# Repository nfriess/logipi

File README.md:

# Code for Logipi FPGA board

This project contains various bits of code for the logpi board.
More information on the board can be found at
http://valentfx.com/logi-pi/

## Projects

- **audio_player**: A basic implementation to stream hifi
  audio from a host PC to a logipi that drives 8 D-to-As.

- **flash_loader**: A utility to load .bit files on the flash
  chip, or read data from the flash chip.

- **i2cslave**: An I2C slave device that can communicate with
  the Raspberry Pi, implementing a wishbone master in VHDL.

- **pi_audio_player**: Playing hifi audio from the Raspberry Pi,
  replacing the audio_player setup with C# and Ethernet.

- **spislave**: An SPI slave device that can communicate with
  the Raspberry Pi, implementing a wishbone master in VHDL.

## License

**Licensed under the GNU GENERAL PUBLIC LICENSE version 2**

Copyright (C) 2016-2017  Nathan Friess

This program is free software; you can redistribute it and/or
modify it under the terms of the GNU General Public License
as published by the Free Software Foundation; either version 2
of the License, or (at your option) any later version.

This program is distributed in the hope that it will be useful,
but WITHOUT ANY WARRANTY; without even the implied warranty of
MERCHANTABILITY or FITNESS FOR A PARTICULAR PURPOSE.  See the
GNU General Public License for more details.

You should have received a copy of the GNU General Public License
along with this program; if not, write to the Free Software
Foundation, Inc., 51 Franklin Street, Fifth Floor, Boston, MA  02110-1301, USA.

http://www.gnu.org/licenses/old-licenses/gpl-2.0-standalone.html

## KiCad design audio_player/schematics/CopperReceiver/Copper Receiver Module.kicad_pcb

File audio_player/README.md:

# Hi-fi Audio Player

A friend of mine has been building Hi-fi audio systems for
a very long time.  Before this project started, his current
system used a custom-designed board around a USB device to
stream audio from a host Windows PC to his custom-built
amplifiers.  Over time the USB device has become too
cumbersome so I have helped design a replacement setup
that will drive his amplifiers using a Logi-PI board.

This project is quite complex so more detailed documentation
is available in the doc directory.

## Architecture

### Hi-fi System

I am not an audiophile, nor do I know the intricacies of
audio amplifier design.  My friend has built some of the
highest quality amplifiers around.

For my part of this system, the only aspects that I need
to know are that there are 8 amplifiers (channels), each
driving a speaker.  The input of an amplifier is an AD1862
D-to-A, which accepts a 20-bit audio.  The Latch Enable
pin is driven by a 44.1 KHz clock, which is divided down
in the FPGA from a standard 16.9344 MHz crystal oscillator.

### Host PC

My friend has written his own audio player program in
C# that he currently uses to stream audio to the Hi-fi
system.  The program reads in raw .WAV files containing
2 channel, 16-bit, 44.1 KHz audio.  It then converts this
to the 8-channel, 20-bit format that will be consumed by
the D-to-As.  It then sends this data over USB, to an
FPGA that drives the D-to-As.

The source code for my friend's audio player is not
available in this repository because that belongs to him.
The project here has a very simple C# program that will
drive the FPGA on the Logi-PI over an Ethernet connection.
He has then taken the core C# class that handles all of the
logic for the Ethernet protocol and integrated that into
his audio player program.

## Logi-Pi Board

Everything in between the host PC and D-to-As, and the
central part of this project.

Although the Logi-Pi board is often paired with a Raspberry
Pi, the Raspberry Pi is is actually not used in the final
product. Instead, a Pi is used to program the flash chip on
the Logi-PI board and was used to debug the VHDL by
monitoring various registers defined in the VHDL.

Other key components required for this project are:

* Digilent PmodNIC100, an add-on board designed around the
  Microchip ENC424J600 Ethernet controller.

* An external 16.9344 MHz crystal to drive the FPGA (for
  proper hi-fi audio).  The FPGA can generate an internal
  clock that is very close to 16.9334 MHz for testing
  purposes.

## Digital Crossover Demo

All of the main parts of this project are focused on the
hardware side, using the Logi-Pi board to drive multiple
DACs.  The "sw" directory provides a minimal example of a
C# program that will transmit audio data to the Logi-Pi
board.  In the final setup of the Hi-fi system, my friend
is driving 6 (and later 8) amplifiers, each outputting only
the ideal frequency range for a particular driver (speaker).
So insteead of using physical parts to create a crossover
for each driver, we do this in C# and send the individual
channel data to the Logi-Pi board, which then drives 6 DACs
independently.

The DigitalCrossoverDemo directory provides an example of
a digital crossover created in C#.  This program does not
work with the Logi-Pi board directly.  Instead it can be
used to listen to and and visual the results of using the
digital crossover code.  It should be trivial to plug this
demo code into the simple player in the sw directory.

The digital crossover is implemented as a chain of audio
filters, following a similar producer-consumer format to
C# Stream sub-classes.  Also included in this project are
a number of other helpful audio filters, such as a volume
control and de-emphasis filter.

The code for crossover filters and de-emphasis filter was
written by Leonard Manzara in C, and ported to C# by me.

## DAC Receiver Board

In the schematics directory is the design for the DAC
receiver board.  That board is part of each amplifier and
is responsible to receive the signals from the Logi-Pi
board and use them to drive the D-to-A in the amplifier.
It uses opto-isolators to keep any electrical noise from
the Logi-Pi separate from the D-to-A.  It also has the
voltage regulators necessary to provide power to the
digital side of the D-to-A.

The voltage regulators are chosen as LT3042 as those are
considered to be some of the best regulators based on
discussions at diyaudio.com.

NOTE: The 47uF capacitors shown in the design are 6V
tolerant but need to be 12V tolerant.  In the next revision
we will need to use a larger footprint on the board to
accommodate the correct capacitor.

## License

### External Libraries

Several pieces of code in VHDL and Verilog were borrowed
from external sources.  Those files will have their own
copyright notices and licenses in the file headers.

These include:

* sdram_controller.v - From opencores.org, GPL license.
  Has been modified slightly to interoperate with other
  parts of the VHDL project.

* control_pack.vhd, logi_primitive_pack.vhd, logi_utils_pack.vhd
  logi_wishbone_pack.vhd, logi_wishbone_peripherals_pack.vhd,
  logipi_r1_5.ucf, spi_wishbone_wrapper.vhd, wishbone_register.vhd:
  From the Logi-PI example code.  Modifed in several places.

* syncflag.vhd, syncsignal.vhd - Based on designs at
  http://www.fpga4fun.com/CrossClockDomain1.html

* dp_sram.vhd - From opencores.org, GPL license.

### New code

Other than the above code, any code produced by me is licensed
as:

**Licensed under the GNU GENERAL PUBLIC LICENSE version 2**

Copyright (C) 2016-2017  Nathan Friess

This program is free software; you can redistribute it and/or
modify it under the terms of the GNU General Public License
as published by the Free Software Foundation; either version 2
of the License, or (at your option) any later version.

This program is distributed in the hope that it will be useful,
but WITHOUT ANY WARRANTY; without even the implied warranty of
MERCHANTABILITY or FITNESS FOR A PARTICULAR PURPOSE.  See the
GNU General Public License for more details.

You should have received a copy of the GNU General Public License
along with this program; if not, write to the Free Software
Foundation, Inc., 51 Franklin Street, Fifth Floor, Boston, MA  02110-1301, USA.

http://www.gnu.org/licenses/old-licenses/gpl-2.0-standalone.html

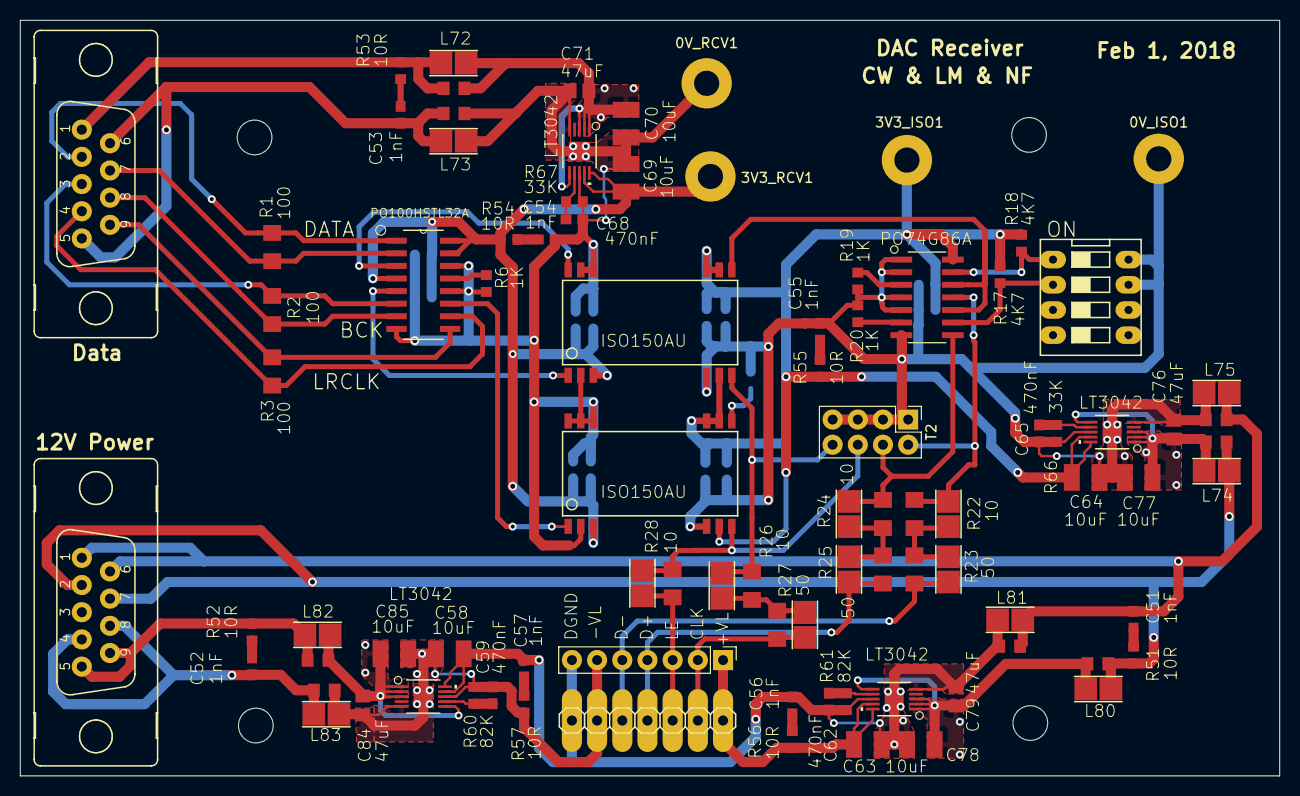
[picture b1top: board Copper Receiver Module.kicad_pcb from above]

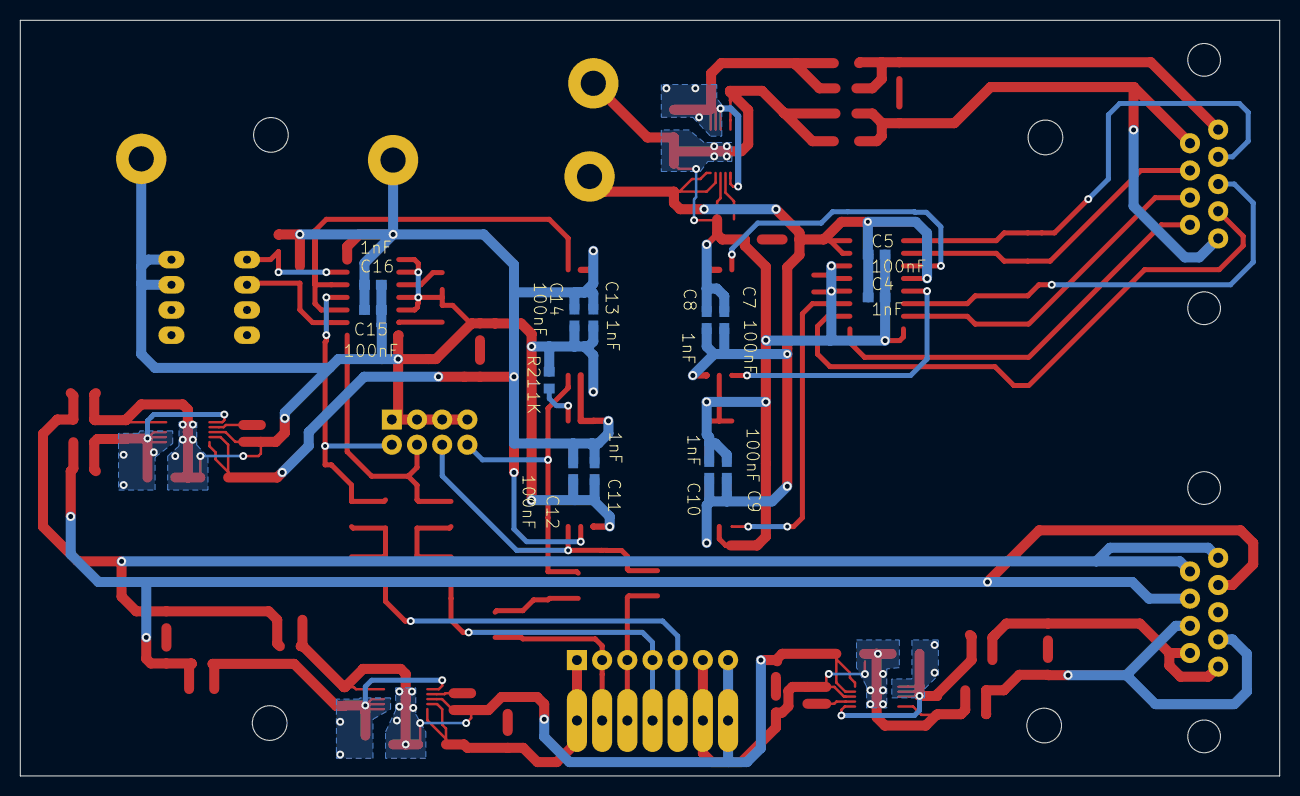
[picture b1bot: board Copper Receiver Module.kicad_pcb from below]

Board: 2 copper layers, 127.0 x 76.2 mm, 103 parts (13 on the bottom side), 55 nets.

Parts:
0V_ISO1, 0V_RCV1, 3V3_ISO1, 3V3_RCV1: Conn_01x01_Female; SinglePad
C4, C8, C10, C11, C13, C16, C51, C52, C53, C54, C55, C56, C57: 1nF; C0603
C5, C7, C9, C12, C14, C15: 100nF; C0603
C58, C63, C64, C69, C70, C77, C78, C85: 10uF; C1210
C59, C62, C65, C68: 470nF; C0603
C71, C76, C79, C84: 47uF; C0805
IC1, IC2, IC3, IC4: LT3042; MSOP-10_MSE
IC5: PO100HSTL32A; SOIC-16
IC7: PO74G86A; SO-14
ISO1, ISO2: ISO150AU; SO28-3-ISO150
JP1: LRCLK; SOLDER-JUMPER_1-WAY
JP2: D-; SOLDER-JUMPER_1-WAY
JP3: D+; SOLDER-JUMPER_1-WAY
JP4: CLK; SOLDER-JUMPER_1-WAY
JP13, JP14, JP15, JP72, JP73, JP74, JP75, JP80, JP81, JP82, JP83: JUMPER-SMT_2_NO_SILK; SOLDER-JUMPER_1-WAY
L72, L73, L74, L75, L80, L81, L82, L83: 60/20/5; RESC0805_N
R1, R2, R3: 100; R1206
R6, R19, R20, R21: 1K; R0603
R17, R18: 4K7; R0603
R22, R24, R26, R28: 10; R1206
R23, R25, R27: 50; R1206
R51, R52, R53, R54, R55, R56, R57: 10R; R0603
R60, R61: 82K; R0603
R66, R67: 33K; R0603
S1: DS04; DS-04_Larger
T1: TERM_07HOLES; TERM_07_HOLES_LARGER
T2: Conn_02x04_Counter_Clockwise; Header_2x4_Larger
T3: Conn_01x07; Pin_Header_1x7_Larger
X1, X2: SubD9; SubD9_Larger

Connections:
0V_ISO: 0V_ISO1.1, C11.2, C12.2, C13.2, C14.2, C15.2, C16.2, C55.2, C64.2, C65.2, C76.2, C77.2, IC4.5, IC4.8, IC4.11, IC7.1, IC7.2, IC7.4, IC7.5, IC7.7, ISO1.12, ISO2.12, JP75.2, L75.1, R19.1, R20.1, R21.1, R66.1, S1.7, S1.8, T2.1, T2.3, T2.5, T2.7
0V_RAW_RECV: C53.2, JP73.1, L73.2, X2.5, X2.6
0V_RECV: 0V_RCV1.1, C4.2, C5.2, C7.2, C8.2, C9.2, C10.2, C54.2, C68.2, C69.2, C70.2, C71.2, IC1.5, IC1.8, IC1.11, IC5.8, IC5.12, IC5.14, ISO1.2, ISO1.26, ISO1.27, ISO2.2, ISO2.26, ISO2.27, ISO2.28, JP73.2, L73.1, R6.1, R67.1
5V_RAW_RECV: JP72.1, L72.2, R53.2, X2.1
+3.3V_ISO: 3V3_ISO1.1, C11.1, C12.1, C13.1, C14.1, C15.1, C16.1, C64.1, IC4.9, IC4.10, IC7.14, ISO1.13, ISO1.16, ISO1.17, ISO2.13, ISO2.16, ISO2.17, R17.1, R18.1, R55.2
+3.3V_RECV: 3V3_RCV1.1, C4.1, C5.1, C7.1, C8.1, C9.1, C10.1, C69.1, IC1.9, IC1.10, IC5.4, IC5.15, IC5.16, ISO1.3, ISO2.3, R54.2
+8.2V_DAC: C63.1, IC2.9, IC2.10, R56.2, T1.+VL, T3.1
-8.2V_DAC: C58.2, C59.2, C84.2, C85.2, IC3.5, IC3.8, IC3.11, JP83.2, L83.1, R57.1, R60.1, T1.-VL, T3.6
/Decoding/BCK+: IC5.6, R2.1, X2.3
/Decoding/D+: JP15.1, R25.1, T1.D+, T3.4
/Decoding/D-: JP14.1, R23.1, T1.D-, T3.5
/Decoding/DATA: IC7.10, IC7.12, ISO1.15
/Decoding/DATA+: IC5.2, R1.2, X2.7
/Decoding/LRCK+: IC5.10, R3.2, X2.4
/Regulated DC Power/1_RAW_0V: C51.2, JP75.1, JP81.1, L75.2, L81.2, X1.1, X1.6
/Regulated DC Power/1_RAW_+12V: JP74.1, JP80.1, L74.2, L80.2, R51.2, X1.2, X1.7
/Regulated DC Power/2_RAW_0V: C52.2, JP83.1, L83.2, X1.4, X1.8
/Regulated DC Power/2_RAW_+12V: JP82.1, L82.2, R52.2, X1.5, X1.9
DGND_DAC: C56.2, C57.2, C58.1, C62.2, C63.2, C78.2, C79.2, IC2.5, IC2.8, IC2.11, IC3.9, IC3.10, JP81.2, L81.1, R61.1, T1.DGND, T3.7
unnamed: C51.1, R51.1
unnamed: C52.1, R52.1
unnamed: C53.1, R53.1
unnamed: C54.1, R54.1
unnamed: C55.1, R55.1
unnamed: C56.1, R56.1
unnamed: C57.1, R57.2
unnamed: C59.1, IC3.7, R60.2
unnamed: C62.1, IC2.7, R61.2
unnamed: C65.1, IC4.7, R66.2
unnamed: C68.1, IC1.7, R67.2
unnamed: C70.1, C71.1, IC1.1, IC1.2, IC1.3, IC1.6, JP72.2, L72.1
unnamed: C76.1, C77.1, IC4.1, IC4.2, IC4.3, IC4.6, JP74.2, L74.1
unnamed: C78.1, C79.1, IC2.1, IC2.2, IC2.3, IC2.6, JP80.2, L80.1
unnamed: C84.1, C85.1, IC3.1, IC3.2, IC3.3, IC3.6, JP82.2, L82.1
unnamed: IC5.1, R1.1, X2.2
unnamed: IC5.3, ISO1.28
unnamed: IC5.5, ISO1.1
unnamed: IC5.7, R2.2, X2.8
unnamed: IC5.9, R3.1, X2.9
unnamed: IC5.11, ISO2.1
unnamed: IC5.13, R6.2
unnamed: IC7.3, R19.2
unnamed: IC7.6, R20.2
unnamed: IC7.8, JP3.2, R24.2, T2.4
unnamed: IC7.9, R17.2, S1.2
unnamed: IC7.11, JP2.2, R22.2, T2.2
unnamed: IC7.13, R18.2, S1.1
unnamed: ISO1.14, JP4.2, R26.1, T2.8
unnamed: ISO2.14, JP1.1, R28.1, T2.6
unnamed: ISO2.15, R21.2
unnamed: JP1.2, R28.2, T1.LE, T3.3
unnamed: JP13.1, R27.2, T1.CLK, T3.2
unnamed: JP4.1, JP13.2, R26.2, R27.1
unnamed: JP2.1, JP14.2, R22.1, R23.2
unnamed: JP3.1, JP15.2, R24.1, R25.2

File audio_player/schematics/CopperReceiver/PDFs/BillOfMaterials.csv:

"Source:","D:\Users\Natman\Documents\KiCad\CopperReceiver\Copper Receiver Module.sch"
"Date:","2/15/2018 6:56:26 PM"
"Tool:","Eeschema (2018-01-07 revision 6cee19d37)-makepkg"
"Component Count:","103"
"Ref","Value","Footprint","Datasheet","Manufacturer","Vendor"
"0V_ISO1","Conn_01x01_Female","CustomParts:SinglePad","","",""
"0V_RCV1","Conn_01x01_Female","CustomParts:SinglePad","","",""
"3V3_ISO1","Conn_01x01_Female","CustomParts:SinglePad","","",""
"3V3_RCV1","Conn_01x01_Female","CustomParts:SinglePad","","",""
"C4","1nF","Capacitors_SMD:C_0603","","","490-1494-1-ND"
"C5","100nF","Capacitors_SMD:C_0603","","","490-1532-1-ND"
"C7","100nF","Capacitors_SMD:C_0603","","","490-1532-1-ND"
"C8","1nF","Capacitors_SMD:C_0603","","","490-1494-1-ND"
"C9","100nF","Capacitors_SMD:C_0603","","","490-1532-1-ND"
"C10","1nF","Capacitors_SMD:C_0603","","","490-1494-1-ND"
"C11","1nF","Capacitors_SMD:C_0603","","","490-1494-1-ND"
"C12","100nF","Capacitors_SMD:C_0603","","","490-1532-1-ND"
"C13","1nF","Capacitors_SMD:C_0603","","","490-1494-1-ND"
"C14","100nF","Capacitors_SMD:C_0603","","","490-1532-1-ND"
"C15","100nF","Capacitors_SMD:C_0603","","","490-1532-1-ND"
"C16","1nF","Capacitors_SMD:C_0603","","","490-1494-1-ND"
"C51","1nF","Capacitors_SMD:C_0603","","","490-1494-1-ND"
"C52","1nF","Capacitors_SMD:C_0603","","","490-1494-1-ND"
"C53","1nF","Capacitors_SMD:C_0603","","","490-1494-1-ND"
"C54","1nF","Capacitors_SMD:C_0603","","","490-1494-1-ND"
"C55","1nF","Capacitors_SMD:C_0603","","","490-1494-1-ND"
"C56","1nF","Capacitors_SMD:C_0603","","","490-1494-1-ND"
"C57","1nF","Capacitors_SMD:C_0603","","","490-1494-1-ND"
"C58","10uF","Capacitors_SMD:C_1210","","","490-1867-1-ND"
"C59","470nF","Capacitors_SMD:C_0603","","","490-3291-1-ND"
"C62","470nF","Capacitors_SMD:C_0603","","","490-3291-1-ND"
"C63","10uF","Capacitors_SMD:C_1210","","","490-1867-1-ND"
"C64","10uF","Capacitors_SMD:C_1210","","","490-1867-1-ND"
"C65","470nF","Capacitors_SMD:C_0603","","","490-3291-1-ND"
"C68","470nF","Capacitors_SMD:C_0603","","","490-3291-1-ND"
"C69","10uF","Capacitors_SMD:C_1210","","","490-1867-1-ND"
"C70","10uF","Capacitors_SMD:C_1210","","","490-1867-1-ND"
"C71","47uF","Capacitors_SMD:C_0805","","","511-1682-1-ND"
"C76","47uF","Capacitors_SMD:C_0805","","","511-1682-1-ND"
"C77","10uF","Capacitors_SMD:C_1210","","","490-1867-1-ND"
"C78","10uF","Capacitors_SMD:C_1210","","","490-1867-1-ND"
"C79","47uF","Capacitors_SMD:C_0805","","","511-1682-1-ND"
"C84","47uF","Capacitors_SMD:C_0805","","","511-1682-1-ND"
"C85","10uF","Capacitors_SMD:C_1210","","","490-1867-1-ND"
"IC1","LT3042","Copper Receiver Module:MSOP-10_MSE","","",""
"IC2","LT3042","Copper Receiver Module:MSOP-10_MSE","","",""
"IC3","LT3042","Copper Receiver Module:MSOP-10_MSE","","",""
"IC4","LT3042","Copper Receiver Module:MSOP-10_MSE","","",""
"IC5","PO100HSTL32A","Copper Receiver Module:SOIC-16","","",""
"IC7","PO74G86A","Copper Receiver Module:SO-14","","",""
"ISO1","ISO150AU","Copper Receiver Module:SO28-3-ISO150","","",""
"ISO2","ISO150AU","Copper Receiver Module:SO28-3-ISO150","","",""
"JP1","LRCLK","CustomParts:SOLDER-JUMPER_1-WAY","","",""
"JP2","D-","CustomParts:SOLDER-JUMPER_1-WAY","","",""
"JP3","D+","CustomParts:SOLDER-JUMPER_1-WAY","","",""
"JP4","CLK","CustomParts:SOLDER-JUMPER_1-WAY","","",""
"JP13","JUMPER-SMT_2_NO_SILK","CustomParts:SOLDER-JUMPER_1-WAY","","",""
"JP14","JUMPER-SMT_2_NO_SILK","CustomParts:SOLDER-JUMPER_1-WAY","","",""
"JP15","JUMPER-SMT_2_NO_SILK","CustomParts:SOLDER-JUMPER_1-WAY","","",""
"JP72","JUMPER-SMT_2_NO_SILK","CustomParts:SOLDER-JUMPER_1-WAY","","",""
"JP73","JUMPER-SMT_2_NO_SILK","CustomParts:SOLDER-JUMPER_1-WAY","","",""
"JP74","JUMPER-SMT_2_NO_SILK","CustomParts:SOLDER-JUMPER_1-WAY","","",""
"JP75","JUMPER-SMT_2_NO_SILK","CustomParts:SOLDER-JUMPER_1-WAY","","",""
"JP80","JUMPER-SMT_2_NO_SILK","CustomParts:SOLDER-JUMPER_1-WAY","","",""
"JP81","JUMPER-SMT_2_NO_SILK","CustomParts:SOLDER-JUMPER_1-WAY","","",""
"JP82","JUMPER-SMT_2_NO_SILK","CustomParts:SOLDER-JUMPER_1-WAY","","",""
"JP83","JUMPER-SMT_2_NO_SILK","CustomParts:SOLDER-JUMPER_1-WAY","","",""
"L72","60/20/5","Copper Receiver Module:RESC0805_N","","","MH2029-600YCT-ND"
"L73","60/20/5","Copper Receiver Module:RESC0805_N","","","MH2029-600YCT-ND"
"L74","60/20/5","Copper Receiver Module:RESC0805_N","","","MH2029-600YCT-ND"
"L75","60/20/5","Copper Receiver Module:RESC0805_N","","","MH2029-600YCT-ND"
"L80","60/20/5","Copper Receiver Module:RESC0805_N","","","MH2029-600YCT-ND"
"L81","60/20/5","Copper Receiver Module:RESC0805_N","","","MH2029-600YCT-ND"
"L82","60/20/5","Copper Receiver Module:RESC0805_N","","","MH2029-600YCT-ND"
"L83","60/20/5","Copper Receiver Module:RESC0805_N","","","MH2029-600YCT-ND"
"R1","100","Resistors_SMD:R_1206","","","RNCP1206FTD100RCT-ND"
"R2","100","Resistors_SMD:R_1206","","","RNCP1206FTD100RCT-ND"
"R3","100","Resistors_SMD:R_1206","","","RNCP1206FTD100RCT-ND"
"R6","1K","Resistors_SMD:R_0603","","","MCT0603-1.00K-CFCT-ND"
"R17","4K7","Resistors_SMD:R_0603","","","MCT0603-4.70K-CFCT-ND"
"R18","4K7","Resistors_SMD:R_0603","","","MCT0603-4.70K-CFCT-ND"
"R19","1K","Resistors_SMD:R_0603","","","MCT0603-1.00K-CFCT-ND"
"R20","1K","Resistors_SMD:R_0603","","","MCT0603-1.00K-CFCT-ND"
"R21","1K","Resistors_SMD:R_0603","","","MCT0603-1.00K-CFCT-ND"
"R22","10","Resistors_SMD:R_1206","","","541-3981-1-ND"
"R23","50","Resistors_SMD:R_1206","","","541-3981-1-ND"
"R24","10","Resistors_SMD:R_1206","","","541-3981-1-ND"
"R25","50","Resistors_SMD:R_1206","","","541-3981-1-ND"
"R26","10","Resistors_SMD:R_1206","","","541-3981-1-ND"
"R27","50","Resistors_SMD:R_1206","","","541-3981-1-ND"
"R28","10","Resistors_SMD:R_1206","","","541-3981-1-ND"
"R51","10R","Resistors_SMD:R_0603","","","MCT0603-10.0-CFCT-ND"
"R52","10R","Resistors_SMD:R_0603","","","MCT0603-10.0-CFCT-ND"
"R53","10R","Resistors_SMD:R_0603","","","MCT0603-10.0-CFCT-ND"
"R54","10R","Resistors_SMD:R_0603","","","MCT0603-10.0-CFCT-ND"
"R55","10R","Resistors_SMD:R_0603","","","MCT0603-10.0-CFCT-ND"
"R56","10R","Resistors_SMD:R_0603","","","MCT0603-10.0-CFCT-ND"
"R57","10R","Resistors_SMD:R_0603","","","MCT0603-10.0-CFCT-ND"
"R60","82K","Resistors_SMD:R_0603","","","749-1684-1-ND"
"R61","82K","Resistors_SMD:R_0603","","","749-1684-1-ND"
"R66","33K","Resistors_SMD:R_0603","","","MCT0603-33.0K-CFCT-ND"
"R67","33K","Resistors_SMD:R_0603","","","MCT0603-33.0K-CFCT-ND"
"S1","DS04","CustomParts:DS-04_Larger","","",""
"T1","TERM_07HOLES","CustomParts:TERM_07_HOLES_LARGER","","",""
"T2","Conn_02x04_Counter_Clockwise","CustomParts:Header_2x4_Larger","","",""
"T3","Conn_01x07","CustomParts:Pin_Header_1x7_Larger","","",""
"X1","SubD9","CustomParts:SubD9_Larger","","",""
"X2","SubD9","CustomParts:SubD9_Larger","","",""

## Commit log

2016-05-15 Initial commit of flash_loader.
2016-05-15 Add MCS file parser for later.
2016-05-23 Add I2C slave device.
2016-05-23 Remove duplicate files.
2016-10-04 Add initial files and top-level READMEs.
2016-10-09 Add documentation.
2016-10-09 Rename i2s to dac.
2016-10-09 Fix pinout for current Logi-Pi rev. Add docs on pinout and how to build and run the project.
2016-10-09 Fix wording in README.
2017-04-11 Rename i2s to dac, since we don't follow the i2s protocol. Fix order of dac output data signals in PMOD connector so they are in a sensible order. Reduce SDRAM buffer size by 1/4 since in practice we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
2017-04-15 Rewrite dac controller states to load registers from SRAM on the first states rather than in the middle. This also corrected the output pins being out of order. Pass start of stream from ethernet thr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
2017-04-27 Reverted the last couple commits where the DAC state machine was rewritten to run continuously. The output sound is now correct again.
2017-06-27 Fix issue with device hanging when playback starts sometimes.
2017-06-30 - Add status sent back to PC if 16M clock is not running - Add pins for mute and 10 minute idle for turning off amp automatically - Add pin that can be turned on and off by PC - Fix bug at end of aud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
2017-07-05 Add registers for volume control and first attempt implementation for left woofer only.
2017-07-05 Increase buffer size after increasing data rate due to 8 channels.
2017-07-09 Upgrade project to Visual Studio 2015, update to 8 channel output.
2017-07-09 Update documentation for recent changes like 8-channel output.
2017-07-12 Add in multipliers to all channels. The channels seem to be rotated by one.
2017-07-18 Fix timing on multiplier, adding one clock cycle before reading output.
2017-07-18 Add simtop to help with simulations.
2017-07-18 Remove parser messages from git.
2017-07-18 Code cleanup. Remove commented out code, add/fix comments, move sdram buffer size to top level module.
2017-08-06 Add missing volumefollow from last commit. Remove debugging signals to reduce the area of the FPGA used. All of these components have been thoroughly debugged by now. Add some attributes to assist th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
2017-08-13 Remove the need for async reset in DAC controller, replacing with a sync reset. Fix missing mute in volume control sensitivity.
2017-08-25 Add digital crossover demo C# project.
2017-08-25 Mention a little more about the filter architecture and de-emphasis.
2017-08-27 Remove async reset in i2cslave and debounce.
2017-08-27 Add randomness into i2c test data so multiple runs will write unique data.
2017-09-27 Make SRAM buffer resizable in prep for adding SPI, invert idle signal so that no power to the logipi board is equivalent to "idle" (ie, the amplifier can be turned off), add more precise timing to SP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
2017-09-27 Add HDL for spislave project.
2017-09-27 Add SPI slave tester and update README with project list.
2017-09-29 Add Raspberry PI code that can use debug registers, SDRAM, etc.
2017-12-15 - Improve debug counter for DAC buffer empty - Fix DAC reset signal not being asserted long enough for SDRAM read counter to reset - Ouptut clock warning to pin
2017-12-20 Rename 16M clk to audio clk since we support multiple frequencies. Split up and clean up main audioclk process.
2017-12-27 User sig defaults to '1'.
2017-12-28 Fix bug where bitclk wasn't being reset when audioclk wraps.
2017-12-31 16M clock was shifting data down too much.
2018-01-01 Make sure bitclk always resets to '0' on the first audioclk state.
2018-01-01 Stop tracking temp files.
2018-01-02 Fix off by 1 issue with bitclk counter, start to improve case where channels may be off and need to realign correctly.
2018-01-29 Add the ability for more clock profiles and more settings, as well as some new profiles to try out different ideas. Also add to UCF async clocks in reverse direction.
2018-02-08 Reduce system clock down to 85MHz and adjust various I/O timings as needed. Attempting to reduce internal timing issues.
2018-03-09 Adjust default timing for end of word.
2018-03-09 Update documentation to reflect current code state.
2018-03-09 Add schematic for DAC reciever.
2018-03-23 Change default clock profile to zeros around falling latch enable. Create precise wait time when resetting DAC controllers to fix a bug where channel outputs were rotated by one after a file plays th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
2018-03-25 Moved ISE to linux, update design goals in ISE.
2018-03-25 Add gitignore.
2018-10-13 Add delay to bitclock to deal with signal skew as seen on receiver board.
2019-04-19 Fix timing of manchester encoding. Data is no longer shifted up one bit relative to lrclk.
2019-05-01 Add 1 bitclk delay to output like manchester branch has to resolve the same kind of timing issue.
2021-04-06 Add docs for communication between Raspberry Pi and Logi-Pi in new setup.
2021-04-06 Document new project.
2021-04-09 Add image of pinout.
